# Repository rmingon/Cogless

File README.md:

<h1 align="center">Cogless</h1>

<p align="center">
  <strong>A single-chip, open-source brushless ESC built around the WCH CH32M007.</strong><br>
  One RISC-V motor-control SoC, six MOSFETs, a handful of passives. Every design file public.
</p>

<p align="center">

</p>

---

## Overview

Most hobby ESCs are black boxes: closed firmware, undocumented hardware, and a microcontroller, gate driver and op-amps spread over a dozen chips. Cogless takes the opposite approach.

The **WCH CH32M007G8R6** integrates on a single die everything the brain of an ESC needs: a RISC-V core, a three-phase 48 V N+N gate pre-driver with bootstrap diodes, the high-voltage and logic regulators, a programmable-gain current amplifier, comparators wired to the PWM timer's emergency brake, and a 3 Msps ADC. The result is a complete motor controller with **one IC, six MOSFETs and a few passives** on a 45 × 40 mm board.

| | |
|---|---|
| **Control** | Sensorless six-step (trapezoidal) commutation, back-EMF sensing |
| **Start-up** | Automatic motor detection and tuning, stored in flash |
| **Protection** | Hardware over-current break, cycle-by-cycle current limit, voltage and thermal derating |
| **Openness** | KiCad sources, fabrication outputs and firmware, dual-licensed |

## Hardware

### Specifications

| Parameter | Value |
|---|---|
| Controller | WCH CH32M007G8R6, QingKe RISC-V, 48 MHz, 62 KB flash, 8 KB RAM, SSOP-28 |
| Gate driver | Integrated three-phase N+N pre-driver, bootstrap diodes, up to 48 V |
| Power stage | 6 × AOD514 (30 V, 46 A, 5.9 mΩ), DPAK, thermal via arrays |
| Supply | 2S to 4S LiPo (6 V to 16.8 V), XT30 connector |
| Regulation | Internal high-voltage LDO and 5 V logic LDO, no external regulator |
| Current sense | 2 mΩ 2512 shunt, Kelvin-routed differential pair, internal PGA (× 16) |
| Voltage sense | Three phase back-EMF dividers and one battery divider, 33 kΩ / 8.2 kΩ (≈ 25 V full scale) |
| Temperature | 10 kΩ B3500 NTC (Cantherm CMFA103J3500HANT) against the low-side MOSFETs |
| Control input | 3-pin header (5 V, GND, signal) |
| Debug | WCH 1-wire SDI (SWIO pad), WCH-LinkE |
| Indicator | Status LED |
| Board | 4 layers, 45 × 40 mm, KiCad 10 |

### Design notes

| Topic | Choice |
|---|---|
| **Current sensing** | The shunt is read differentially: both PGA inputs run as a Kelvin pair straight from the shunt pads, so gate-drive noise and power-trace drops stay out of the measurement. |
| **Hardware over-current** | The PGA output feeds an internal comparator wired to the timer's break input: the bridge shuts down without any software involvement. |
| **Gate safety** | All six MOSFETs have 100 kΩ gate pull-downs, the high sides referenced to their own phase node, so the bridge stays off while the driver powers up. |
| **Sensorless and encoder-ready** | The three phase dividers feed the ADC for back-EMF detection. The control header lands on an ADC and timer-capable pin, ready for an AS5600 or MT6701 encoder. |
| **Supply jumper JP1** | Shorts VHV to VCC12V and bypasses the internal high-voltage regulator, which needs more than 18 V. **JP1 must stay closed for every supported pack, 2S to 4S.** It is bridged by default. |

### Schematic

The full KiCad project (schematic, routed board) and the fabrication outputs (BOM, placement, netlist, Gerber archive) are in [`hardware/`](hardware/).

## Firmware

The firmware lives in [`firmware_DShot/`](firmware_DShot/) as a MounRiver Studio 2 project, with its own [README](firmware_DShot/README.md) covering the internals, the test modes and the bring-up notes.

### Features

| Feature | Description | Status |
|---|---|---|
| Six-step sensorless control | 48 kHz centre-aligned PWM, 400 ns dead time, closed loop on back-EMF zero crossings | Validated at 24 kHz, 48 kHz bench pending |
| Back-EMF sensing | Floating phase sampled in the PWM off-time, against ground | Validated |
| Current sensing | Single shunt, differential PGA, sampled inside the high-side pulse | Validated |
| Motor auto-tune | Start current, noise floor, open-loop acceleration, hand-off speed, closed-loop acceleration | Validated |
| Start-up and arming tones | The motor itself is used as a speaker | Validated |
| Servo PWM input | 1000 to 2000 µs on the control header | Implemented, bench validation pending |
| Load test | Power stage under a real propeller or vehicle load | In progress |
| DShot input, telemetry | Digital throttle protocol | Planned |
| Field-oriented control | Sinusoidal drive from the same hardware | Planned |

### Protections

| Protection | Behaviour |
|---|---|
| Hardware over-current | Comparator to timer break, outputs off immediately |
| Software over-current | Fault after three consecutive samples above the limit |
| Current limiting | Cycle-by-cycle peak limit and slow fold-back |
| Speed ceiling | Duty backed off at the highest speed the sampling can follow |
| Under-voltage | Cell count detected at arming, fold-back then cut-off per cell |
| Over-temperature | Board temperature read every 100 ms, derating from 80 °C, cut-off at 100 °C |
| Loss of signal | Throttle failsafe after 100 ms without a valid pulse |
| Desynchronisation and stall | Outputs off, automatic restart at zero throttle |
| Watchdog | Independent watchdog, 100 ms |

### Current limitations

| Limitation | Detail |
|---|---|
| Speed ceiling | About 80 000 eRPM at 48 kHz (≈ 11 400 rpm on a 14-pole motor), duty limited to about 83 % |
| Load validation | Full-power behaviour under a propeller is still being characterised |

## Getting started

| Step | Action |
|---|---|
| 1 | Order the board from the files in [`hardware/production/`](hardware/production/), or build it from the KiCad sources. |
| 2 | Check that **JP1 is closed**. |
| 3 | Open [`firmware_DShot/`](firmware_DShot/) in MounRiver Studio 2, build, and flash through a WCH-LinkE on SWIO, GND and 5 V. |
| 4 | First power-up on a current-limited supply, motor fixed, **no propeller**. The ESC beeps, then tunes itself to the motor. |
| 5 | Set the throttle source and limits in [`motor_config.h`](firmware_DShot/User/motor_config.h). |

## Repository layout

| Path | Content |
|---|---|
| [`hardware/`](hardware/) | KiCad 10 project: schematic, PCB |
| [`hardware/production/`](hardware/production/) | Fabrication outputs: BOM, placement, netlist, Gerber archive |
| [`firmware_DShot/`](firmware_DShot/) | Firmware, MounRiver Studio 2 project |
| [`firmware_DShot/User/`](firmware_DShot/User/) | Cogless firmware sources |
| [`LICENSE-HARDWARE`](LICENSE-HARDWARE) | CERN-OHL-S v2 |
| [`LICENSE-FIRMWARE`](LICENSE-FIRMWARE) | GPL-3.0 |
| [`LICENSE-COMMERCIAL.md`](LICENSE-COMMERCIAL.md) | Commercial licensing |

The CH32M007 datasheet and reference manual are available from [WCH](https://www.wch-ic.com/products/CH32M007.html).

## Safety

> **Warning.** This is a power-electronics project. LiPo batteries and spinning motors can cause fire and serious injury. Always start on a current-limited supply, keep propellers off during bring-up and auto-tune, and never leave a first power-up unattended. You build and use this design at your own risk.

## Contributing

Issues and pull requests are welcome: layout review, firmware improvements, bring-up reports, or photos of your build. If you spin a variant (higher-voltage MOSFETs, other connectors), open a discussion first: the goal is a family of small, hackable ESCs.

Because Cogless is dual-licensed, a contribution can only be merged if you agree that it may also be distributed under the commercial licence. You keep the copyright of your contribution.

## License

Cogless is **dual-licensed**: open source under strong copyleft licences, or under a commercial licence.

| Part | Open-source licence |
|---|---|
| **Hardware**: everything under [`hardware/`](hardware/) | [CERN-OHL-S v2](LICENSE-HARDWARE) |
| **Firmware**: the files written for Cogless, marked with the Cogless SPDX header | [GPL-3.0-only](LICENSE-FIRMWARE) |

| You want to | Licence |
|---|---|
| Use, study, modify, build or sell Cogless, and publish your modified design files and firmware under the same licences | Open source, free of charge |
| Ship a product based on Cogless without publishing your changes, or combine the firmware with proprietary code | [Commercial licence](LICENSE-COMMERCIAL.md) |

**Third-party files.** The WCH SDK files in `firmware_DShot/Core/`, `Peripheral/`, `Startup/`, `Debug/`, and the `system_ch32v00X.*`, `ch32v00X_it.*` and `ch32v00X_conf.h` files in `User/`, are copyright Nanjing Qinheng Microelectronics (WCH) and remain under WCH's own terms. They are not covered by the Cogless licences.

<p align="center"><sub>Copyright © 2026 Ronan Mingon</sub></p>

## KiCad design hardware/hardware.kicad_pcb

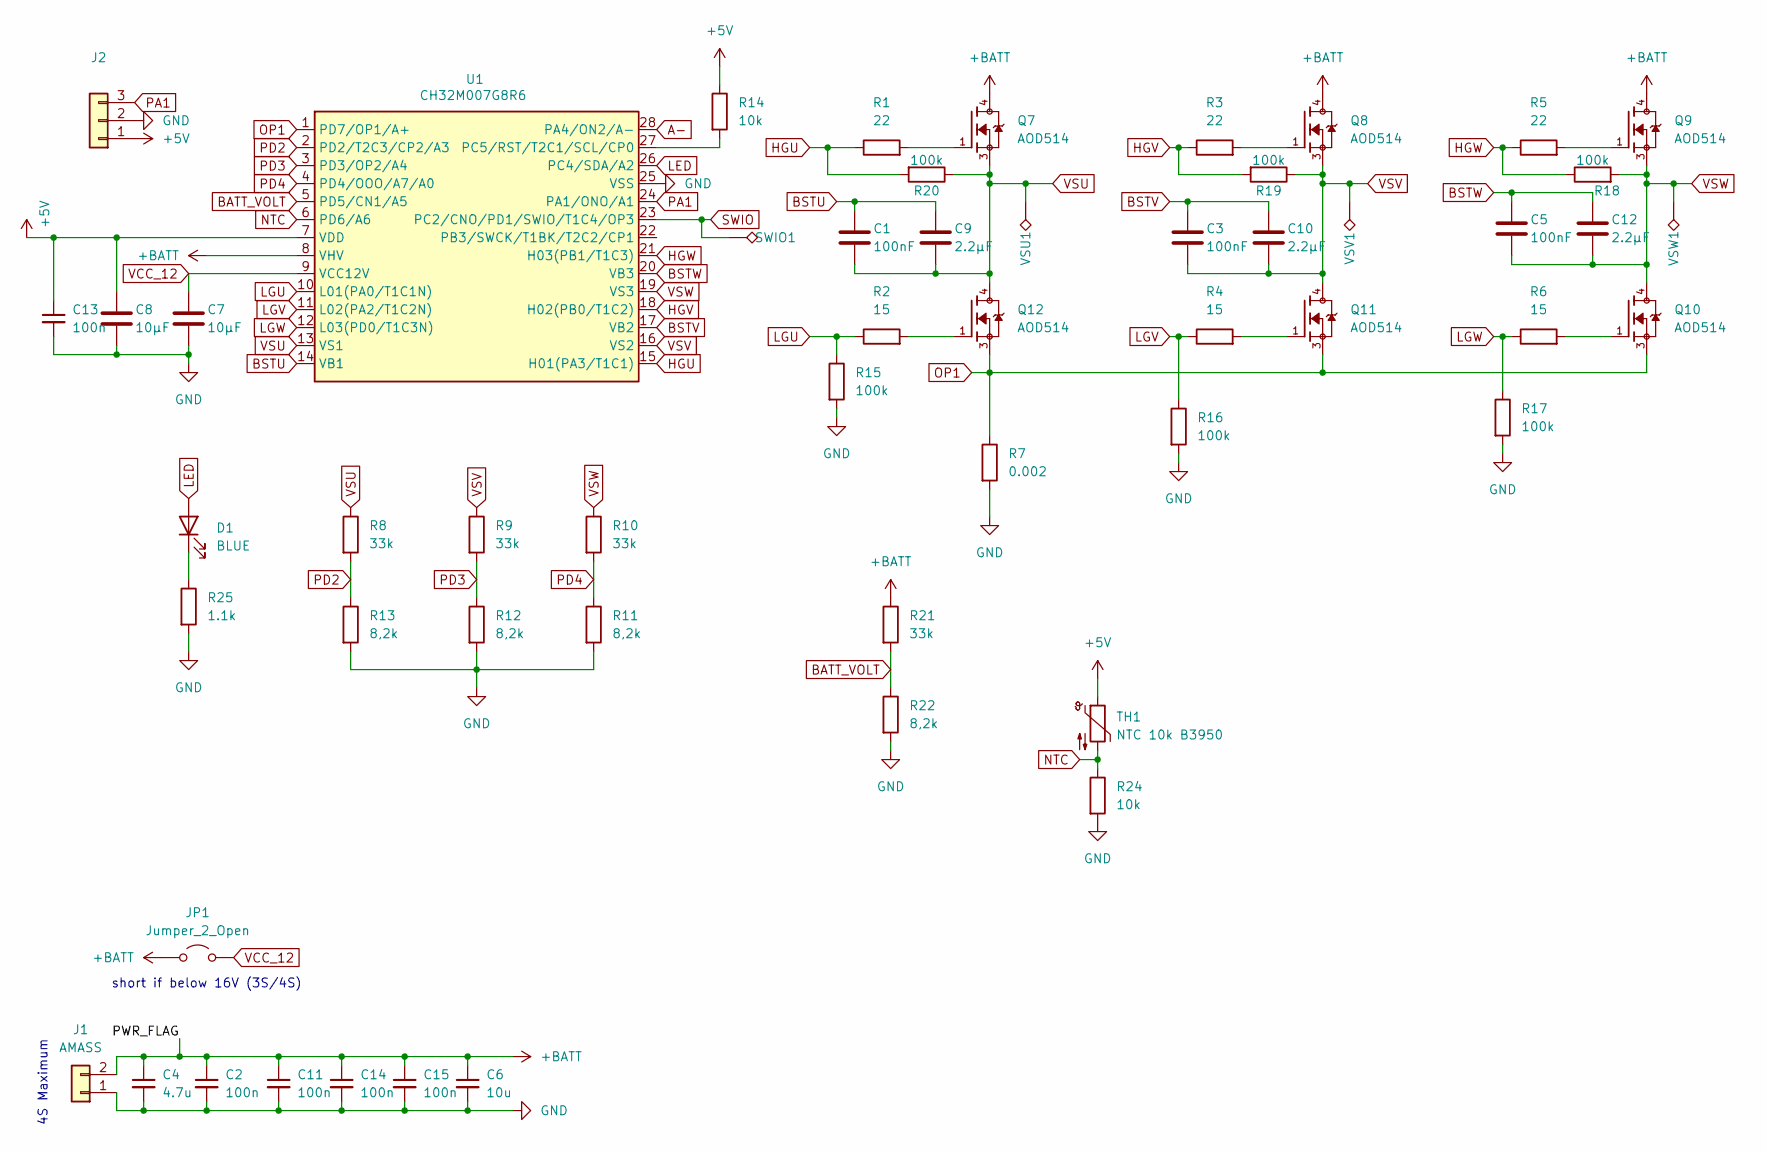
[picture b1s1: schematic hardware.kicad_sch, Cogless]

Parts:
C1, C3, C5: 100nF; C_1206_3216Metric
C2, C11, C14, C15: 100n; C_1206_3216Metric
C4: 4.7u; C_0805_2012Metric
C6: 10u; C_0805_2012Metric
C7, C8: 10µF; C_1206_3216Metric
C9, C10, C12: 2.2µF; C_1206_3216Metric
C13: 100n; C_0805_2012Metric
D1: BLUE; LED_0603_1608Metric
J1: AMASS; AMASS_XT30U-F_1x02_P5.0mm_Vertical
J2: Conn_01x03; PinHeader_1x03_P2.54mm_Vertical
JP1: Jumper_2_Open; SolderJumper-2_P1.3mm_Open_TrianglePad1.0x1.5mm
Q7, Q8, Q9, Q10, Q11, Q12: AOD514; TRANS_AOD514; PARTREV V
R1, R3, R5: 22; R_0603_1608Metric
R2, R4, R6: 15; R_0603_1608Metric
R7: 0.002; R_2512_6332Metric
R8, R9, R10, R21: 33k; R_0603_1608Metric
R11, R12, R13, R22: 8,2k; R_0603_1608Metric
R14, R24: 10k; R_0603_1608Metric
R15, R16, R17, R18, R19, R20: 100k; R_0603_1608Metric
R25: 1.1k; R_0603_1608Metric
SWIO1: TestPoint_Alt; TestPoint_Pad_1.5x1.5mm
TH1: NTC 10k B3950; C_0603_1608Metric
U1: CH32M007G8R6; SSOP-28_3.9x9.9mm_P0.635mm
VSU1: TestPoint_Alt; TestPoint_Pad_3.0x3.0mm
VSV1: TestPoint_Alt; TestPoint_Pad_3.0x3.0mm
VSW1: TestPoint_Alt; TestPoint_Pad_3.0x3.0mm

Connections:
+5V: C8.2, C13.1, J2.1, R14.1, TH1.1, U1.7 (VDD)
+BATT: C2.1, C4.1, C6.1, C11.1, C14.1, C15.1, J1.2, JP1.1 (A), Q7.4, Q8.4, Q9.4, R21.1, U1.8 (VHV)
A-: U1.28 (PA4/ON2/A-)
BATT_VOLT: R21.2, R22.1, U1.5 (PD5/CN1/A5)
BSTU: C1.1, C9.2, U1.14 (VB1)
BSTV: C3.1, C10.2, U1.17 (VB2)
BSTW: C5.1, C12.2, U1.20 (VB3)
GND: C2.2, C4.2, C6.2, C7.1, C8.1, C11.2, C13.2, C14.2, C15.2, J1.1, J2.2, R7.2, R11.2, R12.2, R13.2, R15.2, R16.2, R17.2, R22.2, R24.2, R25.2, U1.25 (VSS)
HGU: R1.1, R20.2, U1.15 (H01(PA3/T1C1))
HGV: R3.1, R19.2, U1.18 (H02(PB0/T1C2))
HGW: R5.1, R18.1, U1.21 (H03(PB1/T1C3))
LED: D1.2 (A), U1.26 (PC4/SDA/A2)
LGU: R2.1, R15.1, U1.10 (L01(PA0/T1C1N))
LGV: R4.1, R16.1, U1.11 (L02(PA2/T1C2N))
LGW: R6.1, R17.1, U1.12 (L03(PD0/T1C3N))
NTC: R24.1, TH1.2, U1.6 (PD6/A6)
unnamed: D1.1 (K), R25.1
unnamed: Q7.1, R1.2
unnamed: Q8.1, R3.2
unnamed: Q9.1, R5.2
unnamed: Q10.1, R6.2
unnamed: Q11.1, R4.2
unnamed: Q12.1, R2.2
unnamed: R14.2, U1.27 (PC5/RST/T2C1/SCL/CP0)
OP1: Q10.3, Q11.3, Q12.3, R7.1, U1.1 (PD7/OP1/A+)
PA1: J2.3, U1.24 (PA1/ONO/A1)
PD2: R8.2, R13.1, U1.2 (PD2/T2C3/CP2/A3)
PD3: R9.2, R12.1, U1.3 (PD3/OP2/A4)
PD4: R10.2, R11.1, U1.4 (PD4/OOO/A7/A0)
SWIO: SWIO1.1 (1_1), U1.23 (PC2/CNO/PD1/SWIO/T1C4/OP3)
VCC_12: C7.2, JP1.2 (B), U1.9 (VCC12V)
VSU: C1.2, C9.1, Q7.3, Q12.4, R8.1, R20.1, U1.13 (VS1), VSU1.1 (1_1)
VSV: C3.2, C10.1, Q8.3, Q11.4, R9.1, R19.1, U1.16 (VS2), VSV1.1 (1_1)
VSW: C5.2, C12.1, Q9.3, Q10.4, R10.1, R18.2, U1.19 (VS3), VSW1.1 (1_1)

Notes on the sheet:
4S Maximum
short if below 16V (3S/4S)

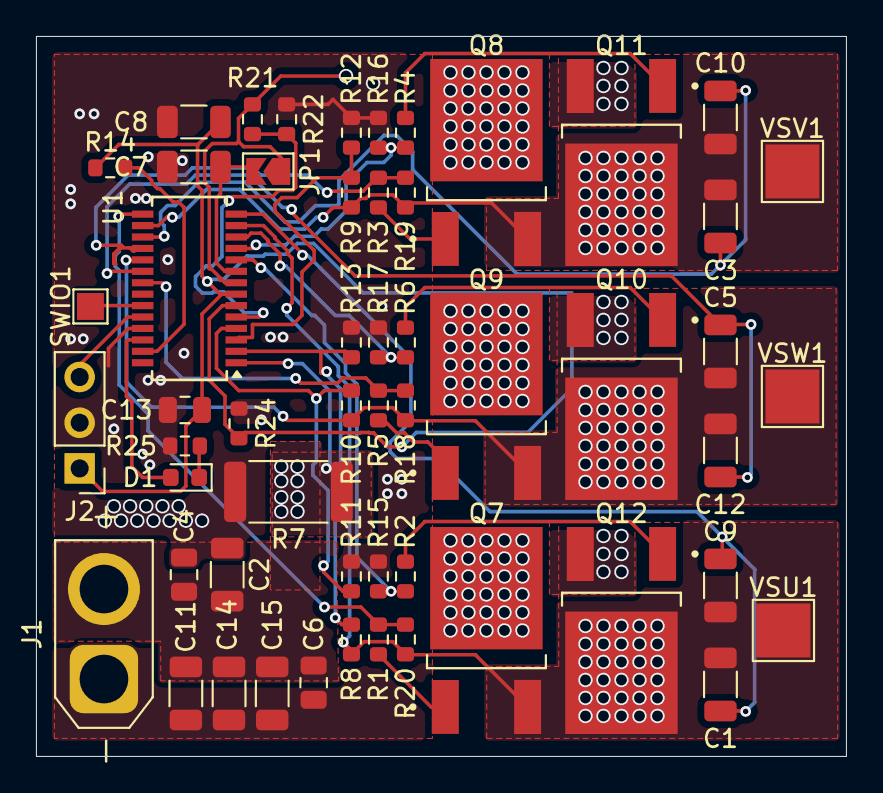
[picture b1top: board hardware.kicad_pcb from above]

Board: 4 copper layers, 45.0 x 40.0 mm, 55 parts (1 on the bottom side), 33 nets.

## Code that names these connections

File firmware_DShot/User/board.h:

/* SPDX-License-Identifier: GPL-3.0-only OR LicenseRef-Cogless-Commercial
 * Copyright (c) 2026 Ronan Mingon */
/*
 * board.h - Cogless ESC hardware definition (CH32M007G8R6, SSOP-28)
 *
 * Every pin below comes from hardware/hardware.kicad_sch. Change this file
 * (and only this file) if the board is re-spun.
 *
 *  Pin  Signal            Net         Function used by the firmware
 *  ---  ----------------  ----------  --------------------------------------------
 *   1   PD7/OPA_P1        OP1         Shunt + (PGA positive input)
 *  28   PA4/OPA_N2        A-          Shunt - Kelvin (PGA negative input, PGADIF)
 *   2   PD2/ADC_IN3       PD2         Phase U back-EMF divider (33k/8.2k)
 *   3   PD3/ADC_IN4       PD3         Phase V back-EMF divider
 *   4   PD4/ADC_IN7       PD4         Phase W back-EMF divider
 *   5   PD5/ADC_IN5       BATT_VOLT   Battery divider (33k/8.2k)
 *   6   PD6/ADC_IN6       NTC         10k B3500 NTC to +5V, 10k to GND
 *  10   LO1 (PA0/T1C1N)   LGU         Low-side gate U
 *  11   LO2 (PA2/T1C2N)   LGV         Low-side gate V
 *  12   LO3 (PD0/T1C3N)   LGW         Low-side gate W
 *  15   HO1 (PA3/T1C1)    HGU         High-side gate U
 *  18   HO2 (PB0/T1C2)    HGV         High-side gate V
 *  21   HO3 (PB1/T1C3)    HGW         High-side gate W
 *  22   PB3/T1BK          n.c.        TIM1 break pin (unused, internal CMP2 used)
 *  23   PC2/PD1/SWIO      SWIO        Debug (TIM1_CH4 lands here with remap 4: keep CC4 output off)
 *  24   PA1/ADC_IN1       PA1         Control input header J2.3 (servo PWM, EXTI1)
 *  26   PC4               LED         Status LED, active high (D1 + 1.1k to GND)
 *  27   PC5/RST           -           Reset, 10k pull-up
 */
#ifndef BOARD_H
#define BOARD_H

#include "ch32v00X.h"

/* ---------------------------------------------------------------- clocks */
#define BOARD_SYSCLK_HZ          48000000UL
#define BOARD_TIM1_CLK_HZ        BOARD_SYSCLK_HZ

/* ------------------------------------------------------------ gate driver
 * TIM1 remap 0100b routes CH1..3 / CH1N..3N to the internal pre-driver
 * (datasheet 1.4.19). GPIO_PartialRemap4_TIM1 == TIM1_RM = 0100b.
 */
#define BOARD_TIM1_REMAP         GPIO_PartialRemap4_TIM1

#define BOARD_HS_U_PORT          GPIOA
#define BOARD_HS_U_PIN           GPIO_Pin_3
#define BOARD_HS_V_PORT          GPIOB
#define BOARD_HS_V_PIN           GPIO_Pin_0
#define BOARD_HS_W_PORT          GPIOB
#define BOARD_HS_W_PIN           GPIO_Pin_1
#define BOARD_LS_U_PORT          GPIOA
#define BOARD_LS_U_PIN           GPIO_Pin_0
#define BOARD_LS_V_PORT          GPIOA
#define BOARD_LS_V_PIN           GPIO_Pin_2
#define BOARD_LS_W_PORT          GPIOD
#define BOARD_LS_W_PIN           GPIO_Pin_0

#define BOARD_BKIN_PORT          GPIOB
#define BOARD_BKIN_PIN           GPIO_Pin_3

/* ---------------------------------------------------------------- analog */
#define BOARD_BEMF_U_PORT        GPIOD
#define BOARD_BEMF_U_PIN         GPIO_Pin_2
#define BOARD_BEMF_U_ADC_CH      ADC_Channel_3
#define BOARD_BEMF_V_PORT        GPIOD
#define BOARD_BEMF_V_PIN         GPIO_Pin_3
#define BOARD_BEMF_V_ADC_CH      ADC_Channel_4
#define BOARD_BEMF_W_PORT        GPIOD
#define BOARD_BEMF_W_PIN         GPIO_Pin_4
#define BOARD_BEMF_W_ADC_CH      ADC_Channel_7

#define BOARD_VBAT_PORT          GPIOD
#define BOARD_VBAT_PIN           GPIO_Pin_5
#define BOARD_VBAT_ADC_CH        ADC_Channel_5

#define BOARD_NTC_PORT           GPIOD
#define BOARD_NTC_PIN            GPIO_Pin_6
#define BOARD_NTC_ADC_CH         ADC_Channel_6

#define BOARD_SHUNT_P_PORT       GPIOD
#define BOARD_SHUNT_P_PIN        GPIO_Pin_7      /* OPA_P1  -> PSEL = CHP1 */
#define BOARD_SHUNT_N_PORT       GPIOA
#define BOARD_SHUNT_N_PIN        GPIO_Pin_4      /* OPA_N2  -> PGADIF = 1 */
#define BOARD_SHUNT_ADC_CH       ADC_Channel_OPA /* internal IN9 */

/* ---------------------------------------------------------- control input */
#define BOARD_RC_PORT            GPIOA
#define BOARD_RC_PIN             GPIO_Pin_1
/* PA1 uses EXTI line 1, not a TIM2 channel: TIM2 remaps 5/6 would take
 * PA0/PA2/PA3 from TIM1 (gate driver). */
#define BOARD_RC_EXTI_LINE       EXTI_Line1

/* ------------------------------------------------------------------- LED */
#define BOARD_LED_PORT           GPIOC
#define BOARD_LED_PIN            GPIO_Pin_4

/* ------------------------------------------------------- scaling factors
 * ADC: 12 bit, VREF = VDD = 5.0 V  -> 1.2207 mV / LSB
 * Phase and battery dividers: 33k / 8.2k -> Vin = Vadc * 41.2 / 8.2
 * Full-scale on the divider: 4096 LSB = 25.1 V (16.8 V pack = 2744 LSB)
 */
#define BOARD_ADC_FULL_SCALE     4096
#define BOARD_VDD_MV             5000
#define BOARD_DIV_TOP_OHM        33000
#define BOARD_DIV_BOT_OHM        8200
/* millivolts = adc * BOARD_VBUS_MV_NUM / BOARD_VBUS_MV_DEN  (6.1333 mV/LSB) */
#define BOARD_VBUS_MV_NUM        6133
#define BOARD_VBUS_MV_DEN        1000

/* Current sense: 2 mOhm shunt, differential PGA x16 with VDD/2 bias.
 * Reference manual table 17-2: AC gain in biased mode = 16 - 0.5 = 15.5.
 * 1 LSB = 1.2207 mV / 15.5 / 2 mOhm = 39.4 mA.  Full scale about +/- 80 A.
 * Zero-current output sits at VDD/2 (about 2048 LSB), calibrated at boot.
 */
#define BOARD_SHUNT_MOHM         2
#define BOARD_PGA_GAIN_X10       155          /* 15.5 */
#define BOARD_I_MA_PER_LSB_NUM   3938         /* 39.38 mA / LSB */
#define BOARD_I_MA_PER_LSB_DEN   100
#define BOARD_I_ZERO_EXPECTED    2048

/* Hardware over-current: CMP2 threshold ~ VDD*30/33 = 4.55 V on the PGA output
 * -> (4.55 - 2.5) / 15.5 / 2 mOhm = about 66 A. Trips TIM1 break directly. */

/* NTC TH1 = Cantherm CMFA103J3500HANT (10k at 25 C, 5 %, B 3500 K) on top,
 * R24 10k to GND: ADC counts rise with temperature.
 * adc = 4096 * 10k / (10k + 10k * exp(B * (1/T - 1/298.15))) */
#define BOARD_NTC_B_K            3500
#define BOARD_NTC_TABLE_T_MIN_C  (-20)
#define BOARD_NTC_TABLE_STEP_C   10
#define BOARD_NTC_TABLE                                                         \
    { 452, 710, 1043, 1431, 1844, 2246, 2609, 2919, 3172, 3373, 3529, 3650, \
      3742, 3814, 3869, 3912, 3946 }                       /* -20 .. 140 C */

#endif /* BOARD_H */
